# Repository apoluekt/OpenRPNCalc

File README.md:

# OpenRPNCalc
Open-source and open-hardware scientific RPN calculator

## Introduction

OpenRPNCalc is a scientific calculator based on the STM32 microcontroller. Its source code, schematics, and PCB design files are released under an open license. The goal is to develop a hardware platform with the following features: 
  * Reproducible without special tools, using only boards produced by PCB prototyping services
  * A customizable keyboard to accommodate specific needs (such as RPN or algebraic logic, custom functions)
  * Low power consumption and long battery life
  * A high-quality, compact and sturdy enclosure

The hardware is inspired by the [SwissMicros](https://www.swissmicros.com/products) calculators, but is designed from scratch. The calculator features: 

  * [Reverse Polish notation](https://www.hpmuseum.org/rpn.htm) with a large stack (up to 100 elements)
  * Double-precision arithmetic
  * "Standard" scientific calculator functions (trigonometric, logarithms, exponentiation, square root and power)
  * Error function (erf) and its inverse (erfinv), Gamma and log(Gamma) functions, combinations and permutations, p-values for Poisson, Gaussian, and chi-squared distributions
  * Fixed, scientific (SCI) and engineering (ENG) display modes (including SI prefixes in ENG mode), with adjustable precision from 3 to 10 digits
  * Calculations with uncertainties using error propagation (UNCERT mode) - a feature rarely found in software calculators and almost unheard of in hardware calculators
  * Formulas from relativistic kinematics (centre-of-mass two-body decay momentum, conversion between angle and pseudorapidity, beta and gamma factors)
  * Statistical functions: mean (or weighted mean in UNCERT mode), RMS, chi-squared of a series of values (only in UNCERT mode). 
  * 100 memory registers
  * Power consumption: 0.6mA running at 16MHz, 16 uA in standby mode with the LCD on, and 5 uA with the LCD off.
  * Optional HP48 keyboard files, with the aim to run [DB48x](https://48calc.org/) (this is still very much WIP)

## Hardware overview

The calculator is built around a low-power 32-bit ARM microcontroller, the [STM32U385](https://www.st.com/en/microcontrollers-microprocessors/stm32u385rg.html). The display is a Sharp memory LCD module, the [LS027B7DH01](https://www.sharpsde.com/products/displays/model/LS027B7DH01/) (400x240 pixel monochrome). The keyboard uses light-touch tactile switches, specifically the Panasonic [EVPBT1C4A000](https://industry.panasonic.com/global/en/products/control/switch/light-touch/number/evpbt1c4a000) (50g actuation force). All electronics are powered by a 3V lithium battery (CR2032), which should be sufficient for several years of operation. 

The enclosure is designed as a stack of multiple PCBs. The front and back panels are aluminium PCBs with a white solder mask and black silkscreen. The keys are also made of PCB, with labels printed as silkscreen. All components are kept together with six M2 standoffs and twelve flat-head screws. The enclosure dimensions are 139 x 73 x 8 mm. 

## Repository contents

   * [Code](Code): STM32 firmware developed using STM32Cube IDE
   * [Hardware](Hardware): Schematic and PCB design files for KiCad, PCB production files
   * [Doc](Doc): Documentation and images
   * [Emulator](Emulator): Online emulator files to be deployed to github-pages or other web hosting

## Documentation

   * [Schematics and parts](Doc/schematics.md) of the PCBs and the list of electronic components and other parts with links to datasheets
   * [PCB design](Doc/pcb_design.md): images of the PCB layers and their functions
   * [Case and keyboard assembly](Doc/assembly.md): photos of the insides of the calculator, assembly instructions
   * [Firmware](Code/README.md): code structure and flashing instructions

## Emulator 

[Online emulator](https://apoluekt.github.io/OpenRPNCalc/Emulator/), based on the original calculator firmware extended with Emscripten and Raylib

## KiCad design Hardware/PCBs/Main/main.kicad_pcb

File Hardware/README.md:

# Hardware design files

Contents of this folder: 

* [PCBs](PCBs): KiCad design files (schematic and PCBs) for all sevel layers. Where appropriate, Python files are also provided to produce silkscreen labels, place components, and make edge cuts.
* [production](production): Production files created in KiCad (Gerber files, bill of materials, position files for assembly service) for each of the 7 PCBs. These can normally be submitted to the PCB prototyping service without modifications.

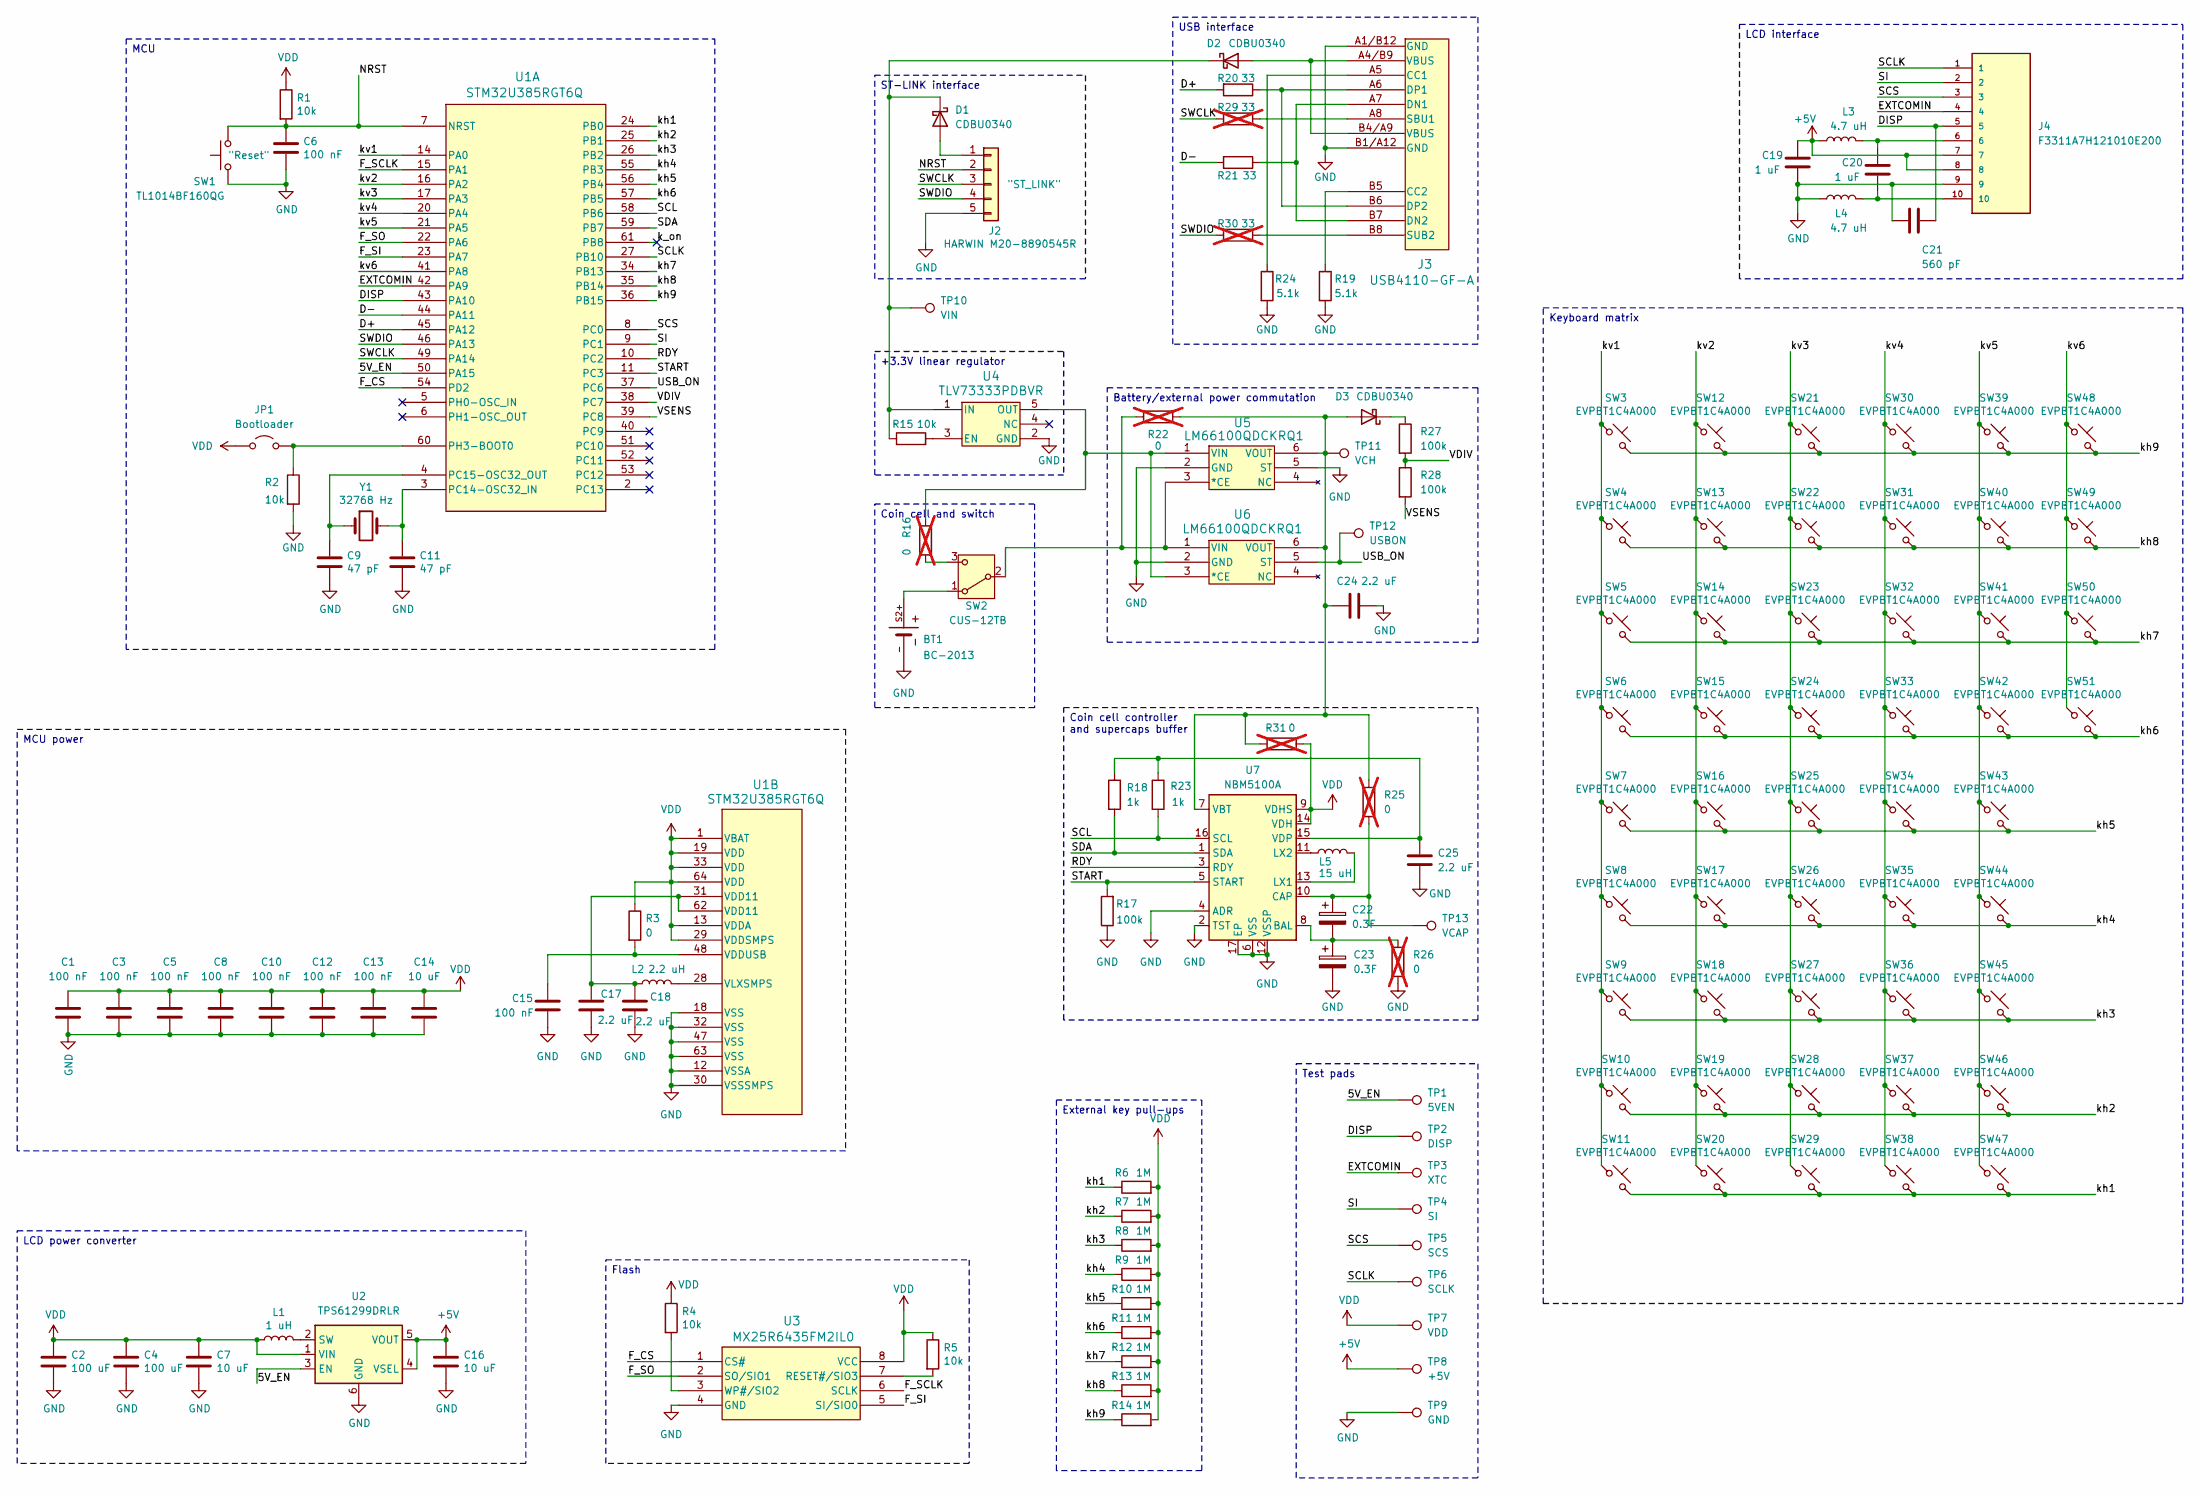
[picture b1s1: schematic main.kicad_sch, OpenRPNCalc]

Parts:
BT1: BC-2013; BAT_BC-2013; PARTREV D
C1, C3, C5, C6, C8, C10, C12, C13, C15: 100 nF; C_0603_1608Metric_Pad1.08x0.95mm_HandSolder
C2, C4: 100 uF; C_0805_2012Metric_Pad1.18x1.45mm_HandSolder
C7, C14, C16: 10 uF; C_0603_1608Metric_Pad1.08x0.95mm_HandSolder
C9, C11: 47 pF; C_0603_1608Metric_Pad1.08x0.95mm_HandSolder
C17, C18, C24, C25: 2.2 uF; C_0603_1608Metric_Pad1.08x0.95mm_HandSolder
C19, C20: 1 uF; C_0603_1608Metric_Pad1.08x0.95mm_HandSolder
C21: 560 pF; C_0603_1608Metric_Pad1.08x0.95mm_HandSolder
C22, C23: 0.3F; Supercap_4x10
D1, D2, D3: CDBU0340; D_0603_1608Metric_Pad1.05x0.95mm_HandSolder
J2: HARWIN M20-8890545R; HARWIN_M20-8890545R
J3: USB4110-GF-A; GCT_USB4110GFA
J4: F3311A7H121010E200; AMPHENOL_F3311A7H121010E200; PARTREV A
JP1: Bootloader; R_0603_1608Metric_Pad0.98x0.95mm_HandSolder
L1: 1 uH; L_0805_2012Metric_Pad1.15x1.40mm_HandSolder
L2: 2.2 uH; L_0805_2012Metric_Pad1.05x1.20mm_HandSolder
L3, L4: 4.7 uH; L_0805_2012Metric_Pad1.15x1.40mm_HandSolder
L5: 15 uH; L_0805_2012Metric_Pad1.05x1.20mm_HandSolder
R1, R2, R4, R5, R15: 10k; R_0603_1608Metric_Pad0.98x0.95mm_HandSolder
R3: 0; R_0603_1608Metric_Pad0.98x0.95mm_HandSolder
R6, R7, R8, R9, R10, R11, R12, R13, R14: 1M; R_0603_1608Metric_Pad0.98x0.95mm_HandSolder
R16, R22, R25, R26, R31: 0; R_0603_1608Metric_Pad0.98x0.95mm_HandSolder; not fitted
R17, R27, R28: 100k; R_0603_1608Metric_Pad0.98x0.95mm_HandSolder
R18, R23: 1k; R_0603_1608Metric_Pad0.98x0.95mm_HandSolder
R19, R24: 5.1k; R_0603_1608Metric_Pad0.98x0.95mm_HandSolder
R20, R21: 33; R_0603_1608Metric_Pad0.98x0.95mm_HandSolder
R29, R30: 33; R_0603_1608Metric_Pad0.98x0.95mm_HandSolder; not fitted
SW1: TL1014BF160QG; TL1014BF160QG_EWI
SW2: CUS-12TB; CUS-12TB_NDC
SW3, SW4, SW5, SW6, SW7, SW8, SW9, SW10, SW11, SW12, SW13, SW14, SW15, SW16, SW17, SW18, SW19, SW20, SW21, SW22, SW23, SW24, SW25, SW26, SW27, SW28, SW29, SW30, SW31, SW32, SW33, SW34, SW35, SW36, SW37, SW38, SW39, SW40, SW41, SW42, SW43, SW44, SW45, SW46, SW47, SW48, SW49, SW50, SW51: EVPBT1C4A000; SW_SPST_EVQQ2
TP1: 5VEN; TestPoint_Pad_D2.0mm
TP2: DISP; TestPoint_Pad_D2.0mm
TP3: XTC; TestPoint_Pad_D2.0mm
TP4: SI; TestPoint_Pad_D2.0mm
TP5: SCS; TestPoint_Pad_D2.0mm
TP6: SCLK; TestPoint_Pad_D2.0mm
TP7: VDD; TestPoint_Pad_D2.0mm
TP8: +5V; TestPoint_Pad_D2.0mm
TP9: GND; TestPoint_Pad_D2.0mm
TP10: VIN; TestPoint_Pad_D2.0mm
TP11: VCH; TestPoint_Pad_D2.0mm
TP12: USBON; TestPoint_Pad_D2.0mm
TP13: VCAP; TestPoint_Pad_D2.0mm
U1: STM32U385RGT6Q; LQFP64_STM
U2: TPS61299DRLR; SOT-563
U3: MX25R6435FM2IL0; SOP_8L_200_MAC
U4: TLV73333PDBVR; DBV0005A_N
U5, U6: LM66100QDCKRQ1; SC70-6_DCK_TEX
U7: NBM5100A; DHVQFN-16-1EP_2.5x3.5mm_P0.5mm_EP1x2mm
Y1: 32768 Hz; Crystal_SMD_2012-2Pin_2.0x1.2mm_HandSoldering

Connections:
+5V: C16.1, C19.1, J4.7, J4.8, L3.1, TP8.1, U2.4 (VSEL), U2.5 (VOUT)
/5V_EN: TP1.1, U1.50 (PA15), U2.3 (EN)
/D+: R20.2, U1.45 (PA12)
/D-: R21.2, U1.44 (PA11)
/DISP: C21.1, J4.5, TP2.1, U1.43 (PA10)
/EXTCOMIN: J4.4, TP3.1, U1.42 (PA9)
/F_CS: U1.54 (PD2), U3.1 (CS#)
/F_SCLK: U1.15 (PA1), U3.6 (SCLK)
/F_SI: U1.23 (PA7), U3.5 (SI/SIO0)
/F_SO: U1.22 (PA6), U3.2 (SO/SIO1)
/NRST: C6.1, J2.2, R1.2, SW1.1, U1.7 (NRST)
/RDY: U1.10 (PC2), U7.3 (RDY)
/SCL: R23.2, U1.58 (PB6), U7.16 (SCL)
/SCLK: J4.1, TP6.1, U1.27 (PB10)
/SCS: J4.3, TP5.1, U1.8 (PC0)
/SDA: R18.2, U1.59 (PB7), U7.1 (SDA)
/SI: J4.2, TP4.1, U1.9 (PC1)
/START: R17.2, U1.11 (PC3), U7.5 (START)
/SWCLK: J2.3, R29.2, U1.49 (PA14)
/SWDIO: J2.4, R30.2, U1.46 (PA13)
/USB_ON: TP12.1, U1.37 (PC6), U6.5 (ST)
/VDIV: R27.2, R28.1, U1.38 (PC7)
/VSENS: R28.2, U1.39 (PC8)
/k_on: U1.61 (PB8)
/kh1: R6.1, SW11.2, SW20.2, SW29.2, SW38.2, SW47.2, U1.24 (PB0)
/kh2: R7.1, SW10.2, SW19.2, SW28.2, SW37.2, SW46.2, U1.25 (PB1)
/kh3: R8.1, SW9.2, SW18.2, SW27.2, SW36.2, SW45.2, U1.26 (PB2)
/kh4: R9.1, SW8.2, SW17.2, SW26.2, SW35.2, SW44.2, U1.55 (PB3)
/kh5: R10.1, SW7.2, SW16.2, SW25.2, SW34.2, SW43.2, U1.56 (PB4)
/kh6: R11.1, SW6.2, SW15.2, SW24.2, SW33.2, SW42.2, SW51.2, U1.57 (PB5)
/kh7: R12.1, SW5.2, SW14.2, SW23.2, SW32.2, SW41.2, SW50.2, U1.34 (PB13)
/kh8: R13.1, SW4.2, SW13.2, SW22.2, SW31.2, SW40.2, SW49.2, U1.35 (PB14)
/kh9: R14.1, SW3.2, SW12.2, SW21.2, SW30.2, SW39.2, SW48.2, U1.36 (PB15)
/kv1: SW3.1, SW4.1, SW5.1, SW6.1, SW7.1, SW8.1, SW9.1, SW10.1, SW11.1, U1.14 (PA0)
/kv2: SW12.1, SW13.1, SW14.1, SW15.1, SW16.1, SW17.1, SW18.1, SW19.1, SW20.1, U1.16 (PA2)
/kv3: SW21.1, SW22.1, SW23.1, SW24.1, SW25.1, SW26.1, SW27.1, SW28.1, SW29.1, U1.17 (PA3)
/kv4: SW30.1, SW31.1, SW32.1, SW33.1, SW34.1, SW35.1, SW36.1, SW37.1, SW38.1, U1.20 (PA4)
/kv5: SW39.1, SW40.1, SW41.1, SW42.1, SW43.1, SW44.1, SW45.1, SW46.1, SW47.1, U1.21 (PA5)
/kv6: SW48.1, SW49.1, SW50.1, SW51.1, U1.41 (PA8)
GND: BT1.-, C1.1, C2.2, C3.1, C4.2, C5.1, C6.2, C7.2, C8.1, C9.2, C10.1, C11.2, C12.1, C13.1, C14.1, C15.2, C16.2, C17.2, C18.2, C19.2, C21.2, C23.2, C24.2, C25.2, J2.5, J3.A1/B12 (GND), J3.B1/A12 (GND), J4.9, L4.1, R2.2, R17.1, R19.2, R24.2, R26.2, SW1.2, TP9.1, U1.12 (VSSA), U1.18 (VSS), U1.30 (VSSSMPS), U1.32 (VSS), U1.47 (VSS), U1.63 (VSS), U2.6 (GND), U3.4 (GND), U4.2 (GND), U5.2 (GND), U5.5 (ST), U6.2 (GND), U7.2 (TST), U7.4 (ADR), U7.6 (VSS), U7.12 (VSSP), U7.17 (EP)
unnamed: C17.1, C18.1, L2.1, U1.31 (VDD11), U1.62 (VDD11)
unnamed: C20.1, J4.6, L3.2
unnamed: C20.2, J4.10, L4.2
unnamed: D1.2 (A), J2.1
unnamed: D1.1 (K), D2.1 (K), R15.1, TP10.1, U4.1 (IN)
unnamed: D2.2 (A), J3.A4/B9 (VBUS), J3.B4/A9 (VBUS)
unnamed: C24.1, D3.2 (A), R22.1, R25.1, R31.1, TP11.1, U5.6 (VOUT), U6.6 (VOUT), U7.7 (VBT)
unnamed: D3.1 (K), R27.1
unnamed: J3.A5 (CC1), R24.1
unnamed: J3.B5 (CC2), R19.1
unnamed: J3.A7 (DN1), J3.B7 (DN2), R21.1
unnamed: J3.A6 (DP1), J3.B6 (DP2), R20.1
unnamed: J3.A8 (SBU1), R29.1
unnamed: J3.B8 (SUB2), R30.1
unnamed: JP1.2 (B), R2.1, U1.60 (PH3-BOOT0)
unnamed: BT1.S2+, SW2.1 (A)
unnamed: R22.2, SW2.2 (B), U5.3 (*CE), U6.1 (VIN)
unnamed: R16.1, SW2.3 (C)
unnamed: C11.1, U1.3 (PC14-OSC32_IN), Y1.2
unnamed: C9.1, U1.4 (PC15-OSC32_OUT), Y1.1
unnamed: C15.1, R3.2, U1.48 (VDDUSB)
unnamed: L2.2, U1.28 (VLXSMPS)
unnamed: L1.2, U2.2 (SW)
unnamed: R5.2, U3.7 (RESET#/SIO3)
unnamed: R4.2, U3.3 (WP#/SIO2)
unnamed: R15.2, U4.3 (EN)
unnamed: R16.2, U4.5 (OUT), U5.1 (VIN), U6.3 (*CE)
unnamed: C22.2, C23.1, R26.1, U7.8 (BAL)
unnamed: C22.1, R25.2, TP13.1, U7.10 (CAP)
unnamed: L5.2, U7.13 (LX1)
unnamed: L5.1, U7.11 (LX2)
unnamed: C25.1, R18.1, R23.1, U7.15 (VDP)
VDD: C1.2, C2.1, C3.2, C4.1, C5.2, C7.1, C8.2, C10.2, C12.2, C13.2, C14.2, JP1.1 (A), L1.1, R1.1, R3.1, R4.1, R5.1, R6.2, R7.2, R8.2, R9.2, R10.2, R11.2, R12.2, R13.2, R14.2, R31.2, TP7.1, U1.1 (VBAT), U1.13 (VDDA), U1.19 (VDD), U1.29 (VDDSMPS), U1.33 (VDD), U1.64 (VDD), U2.1 (VIN), U3.8 (VCC), U7.9 (VDHS), U7.14 (VDH)

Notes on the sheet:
MCU
Keyboard matrix
+3.3V linear regulator
Flash
LCD interface
MCU power
Battery/external power commutation
Coin cell controller and supercaps buffer
Coin cell and switch
ST-LINK interface
Test pads
LCD power converter
USB interface
External key pull-ups

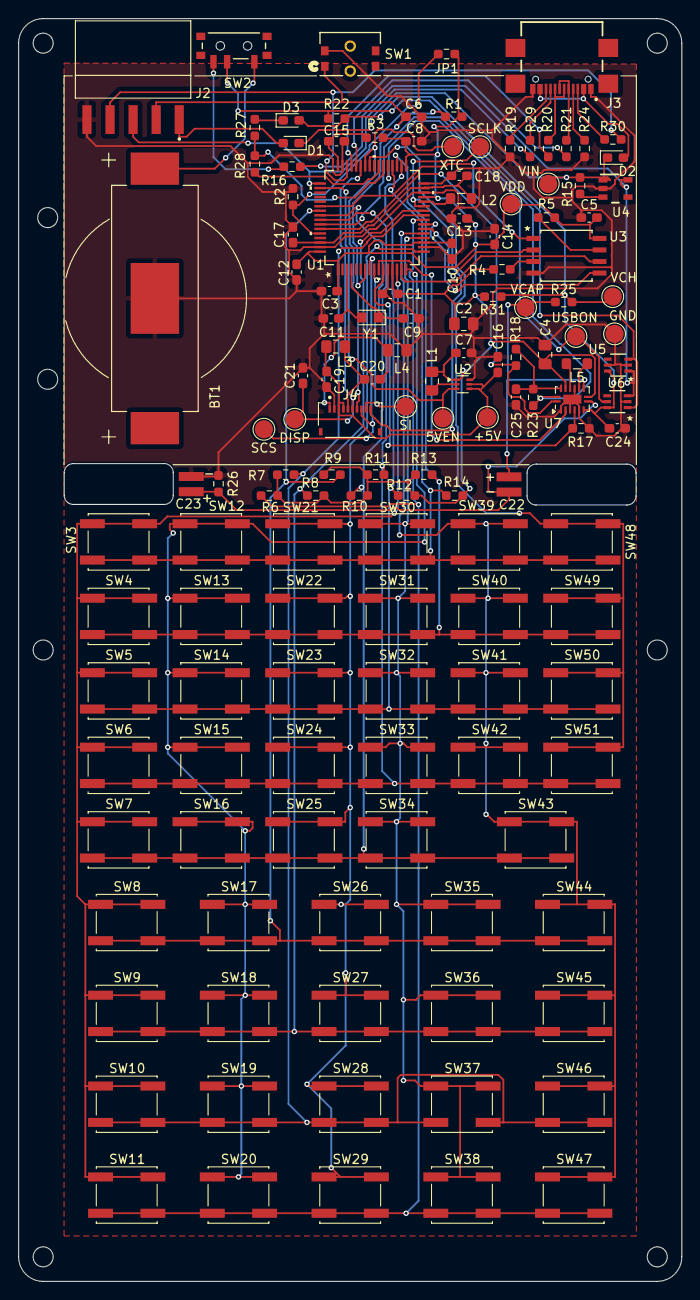
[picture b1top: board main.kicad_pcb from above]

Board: 2 copper layers, 73.0 x 139.0 mm, 141 parts (0 on the bottom side), 72 nets.

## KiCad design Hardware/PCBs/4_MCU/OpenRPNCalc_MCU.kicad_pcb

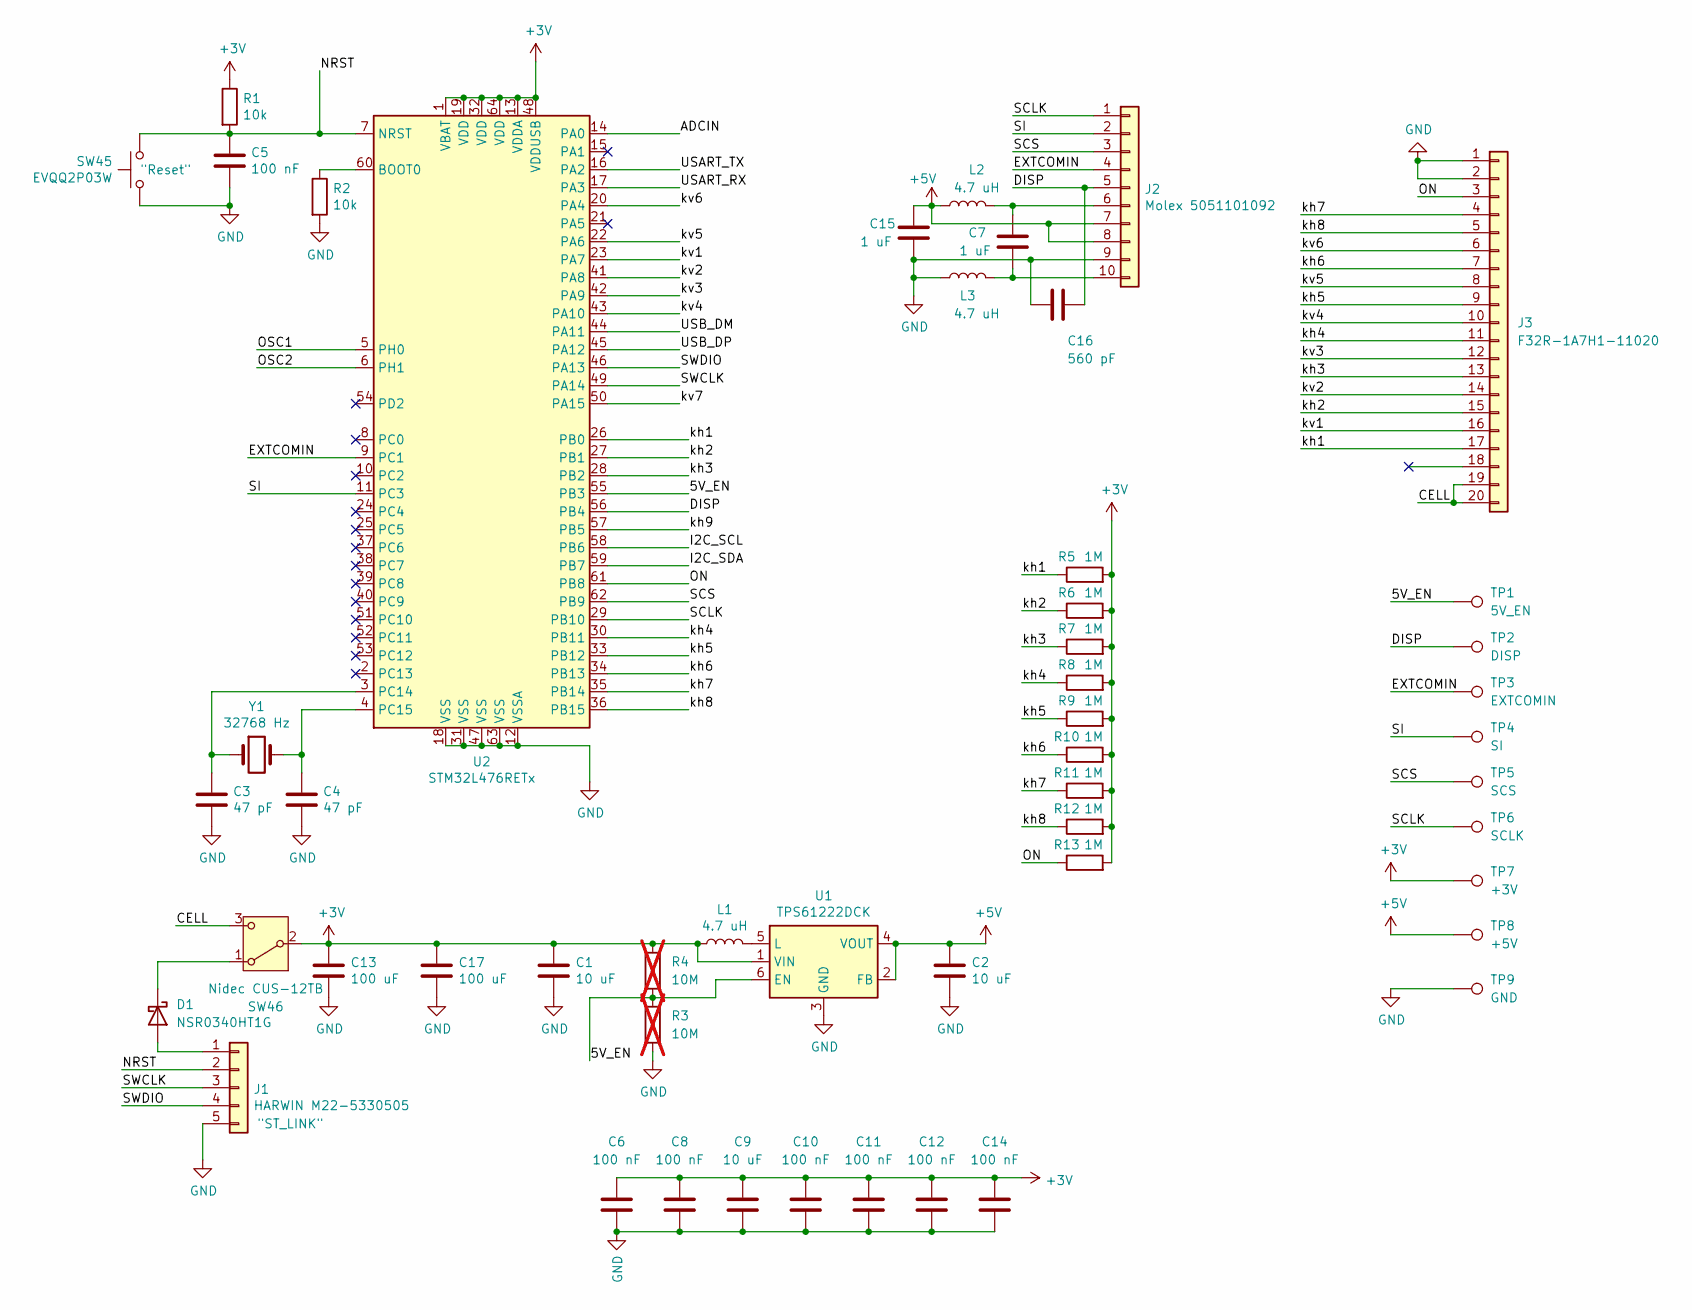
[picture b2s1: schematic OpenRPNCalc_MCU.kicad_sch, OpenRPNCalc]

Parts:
C1, C2, C9: 10 uF; C_0603_1608Metric_Pad1.08x0.95mm_HandSolder
C3, C4: 47 pF; C_0603_1608Metric_Pad1.08x0.95mm_HandSolder
C5, C6, C8, C10, C11, C12, C14: 100 nF; C_0603_1608Metric_Pad1.08x0.95mm_HandSolder
C7, C15: 1 uF; C_0603_1608Metric_Pad1.08x0.95mm_HandSolder
C13, C17: 100 uF; C_1206_3216Metric_Pad1.33x1.80mm_HandSolder
C16: 560 pF; C_0603_1608Metric_Pad1.08x0.95mm_HandSolder
D1: NSR0340HT1G; D_SOD-323_HandSoldering
J1: HARWIN M22-5330505; HARWIN_M22-5330505
J2: Molex 5051101092; CON_5051101092_MOL
J3: F32R-1A7H1-11020; AMPHENOL_F32R-1A7H1-11020
L1, L2, L3: 4.7 uH; L_0805_2012Metric_Pad1.15x1.40mm_HandSolder
R1, R2: 10k; R_0603_1608Metric_Pad0.98x0.95mm_HandSolder
R3, R4: 10M; R_0603_1608Metric_Pad0.98x0.95mm_HandSolder; not fitted
R5, R6, R7, R8, R9, R10, R11, R12, R13: 1M; R_0603_1608Metric_Pad0.98x0.95mm_HandSolder
SW45: EVQQ2P03W; SW_SPST_EVQQ2
SW46: Nidec CUS-12TB; CUS-12TB_NDC
TP1: 5V_EN; TestPoint_Pad_D2.0mm
TP2: DISP; TestPoint_Pad_D2.0mm
TP3: EXTCOMIN; TestPoint_Pad_D2.0mm
TP4: SI; TestPoint_Pad_D2.0mm
TP5: SCS; TestPoint_Pad_D2.0mm
TP6: SCLK; TestPoint_Pad_D2.0mm
TP7: +3V; TestPoint_Pad_D2.0mm
TP8: +5V; TestPoint_Pad_D2.0mm
TP9: GND; TestPoint_Pad_D2.0mm
U1: TPS61222DCK; Texas_R-PDSO-G6
U2: STM32L476RETx; LQFP-64_10x10mm_P0.5mm
Y1: 32768 Hz; Crystal_SMD_2012-2Pin_2.0x1.2mm_HandSoldering

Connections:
+5V: C2.1, C15.1, J2.7, J2.8, L2.1, TP8.1, U1.2 (FB), U1.4 (VOUT)
+BATT: C1.1, C6.2, C8.2, C9.2, C10.2, C11.2, C12.2, C13.1, C14.2, C17.1, L1.1, R1.1, R4.1, R5.2, R6.2, R7.2, R8.2, R9.2, R10.2, R11.2, R12.2, R13.2, SW46.2 (B), TP7.1, U1.1 (VIN), U2.1 (VBAT), U2.13 (VDDA), U2.19 (VDD), U2.32 (VDD), U2.48 (VDDUSB), U2.64 (VDD)
/5V_EN: R3.1, R4.2, TP1.1, U1.6 (EN), U2.55 (PB3)
/ADCIN: U2.14 (PA0)
/CELL: J3.19, J3.20, SW46.3 (C)
/DISP: C16.1, J2.5, TP2.1, U2.56 (PB4)
/EXTCOMIN: J2.4, TP3.1, U2.9 (PC1)
/I2C_SCL: U2.58 (PB6)
/I2C_SDA: U2.59 (PB7)
/NRST: C5.1, J1.2, R1.2, SW45.1, U2.7 (NRST)
/ON: J3.3, R13.1, U2.61 (PB8)
/OSC1: U2.5 (PH0)
/OSC2: U2.6 (PH1)
/SCLK: J2.1, TP6.1, U2.29 (PB10)
/SCS: J2.3, TP5.1, U2.62 (PB9)
/SI: J2.2, TP4.1, U2.11 (PC3)
/SWCLK: J1.3, U2.49 (PA14)
/SWDIO: J1.4, U2.46 (PA13)
/USART_RX: U2.17 (PA3)
/USART_TX: U2.16 (PA2)
/USB_DM: U2.44 (PA11)
/USB_DP: U2.45 (PA12)
/kh1: J3.17, R5.1, U2.26 (PB0)
/kh2: J3.15, R6.1, U2.27 (PB1)
/kh3: J3.13, R7.1, U2.28 (PB2)
/kh4: J3.11, R8.1, U2.30 (PB11)
/kh5: J3.9, R9.1, U2.33 (PB12)
/kh6: J3.7, R10.1, U2.34 (PB13)
/kh7: J3.4, R11.1, U2.35 (PB14)
/kh8: J3.5, R12.1, U2.36 (PB15)
/kh9: U2.57 (PB5)
/kv1: J3.16, U2.23 (PA7)
/kv2: J3.14, U2.41 (PA8)
/kv3: J3.12, U2.42 (PA9)
/kv4: J3.10, U2.43 (PA10)
/kv5: J3.8, U2.22 (PA6)
/kv6: J3.6, U2.20 (PA4)
/kv7: U2.50 (PA15)
GND: C1.2, C2.2, C3.2, C4.2, C5.2, C6.1, C8.1, C9.1, C10.1, C11.1, C12.1, C13.2, C14.1, C15.2, C16.2, C17.2, J1.5, J2.9, J3.1, J3.2, L3.1, R2.2, R3.2, SW45.2, TP9.1, U1.3 (GND), U2.12 (VSSA), U2.18 (VSS), U2.31 (VSS), U2.47 (VSS), U2.63 (VSS)
unnamed: D1.2 (A), J1.1
unnamed: D1.1 (K), SW46.1 (A)
unnamed: C7.1, J2.6, L2.2
unnamed: C7.2, J2.10, L3.2
unnamed: L1.2, U1.5 (L)
unnamed: R2.1, U2.60 (BOOT0)
unnamed: C3.1, U2.3 (PC14), Y1.1
unnamed: C4.1, U2.4 (PC15), Y1.2

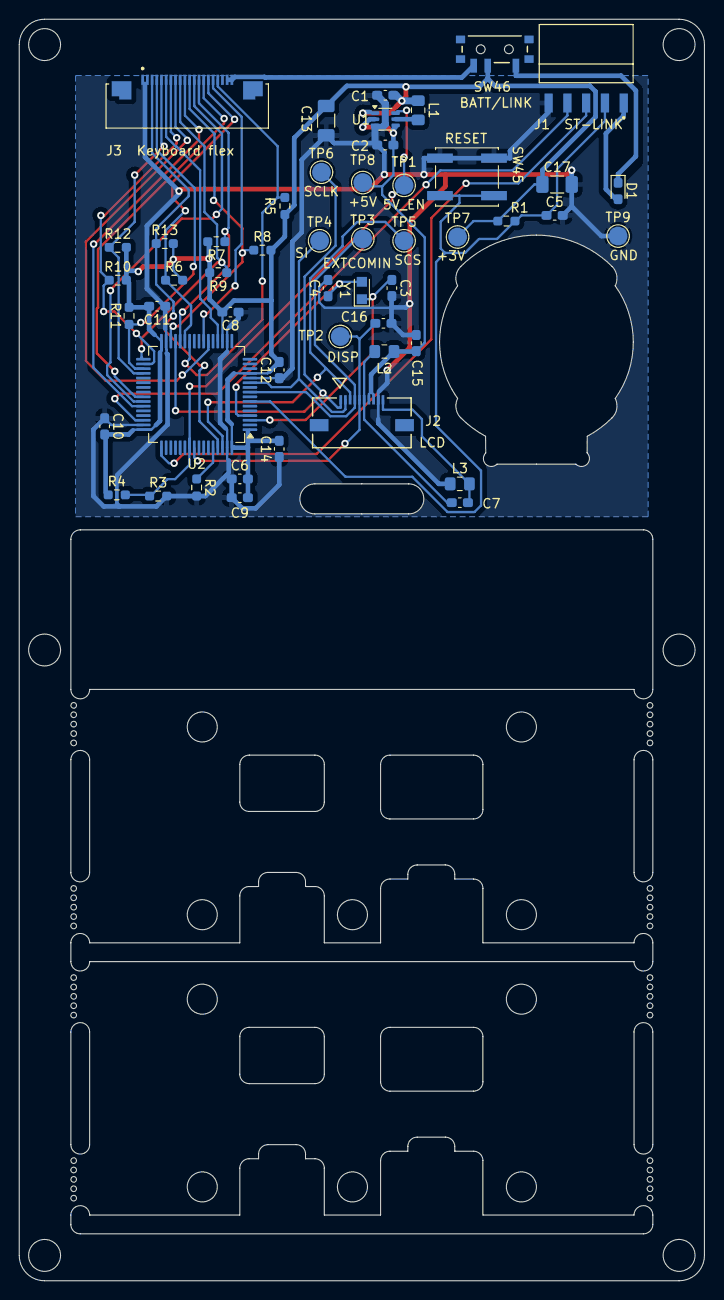
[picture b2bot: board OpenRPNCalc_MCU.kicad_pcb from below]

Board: 2 copper layers, 73.0 x 134.4 mm, 51 parts (51 on the bottom side), 36 nets.

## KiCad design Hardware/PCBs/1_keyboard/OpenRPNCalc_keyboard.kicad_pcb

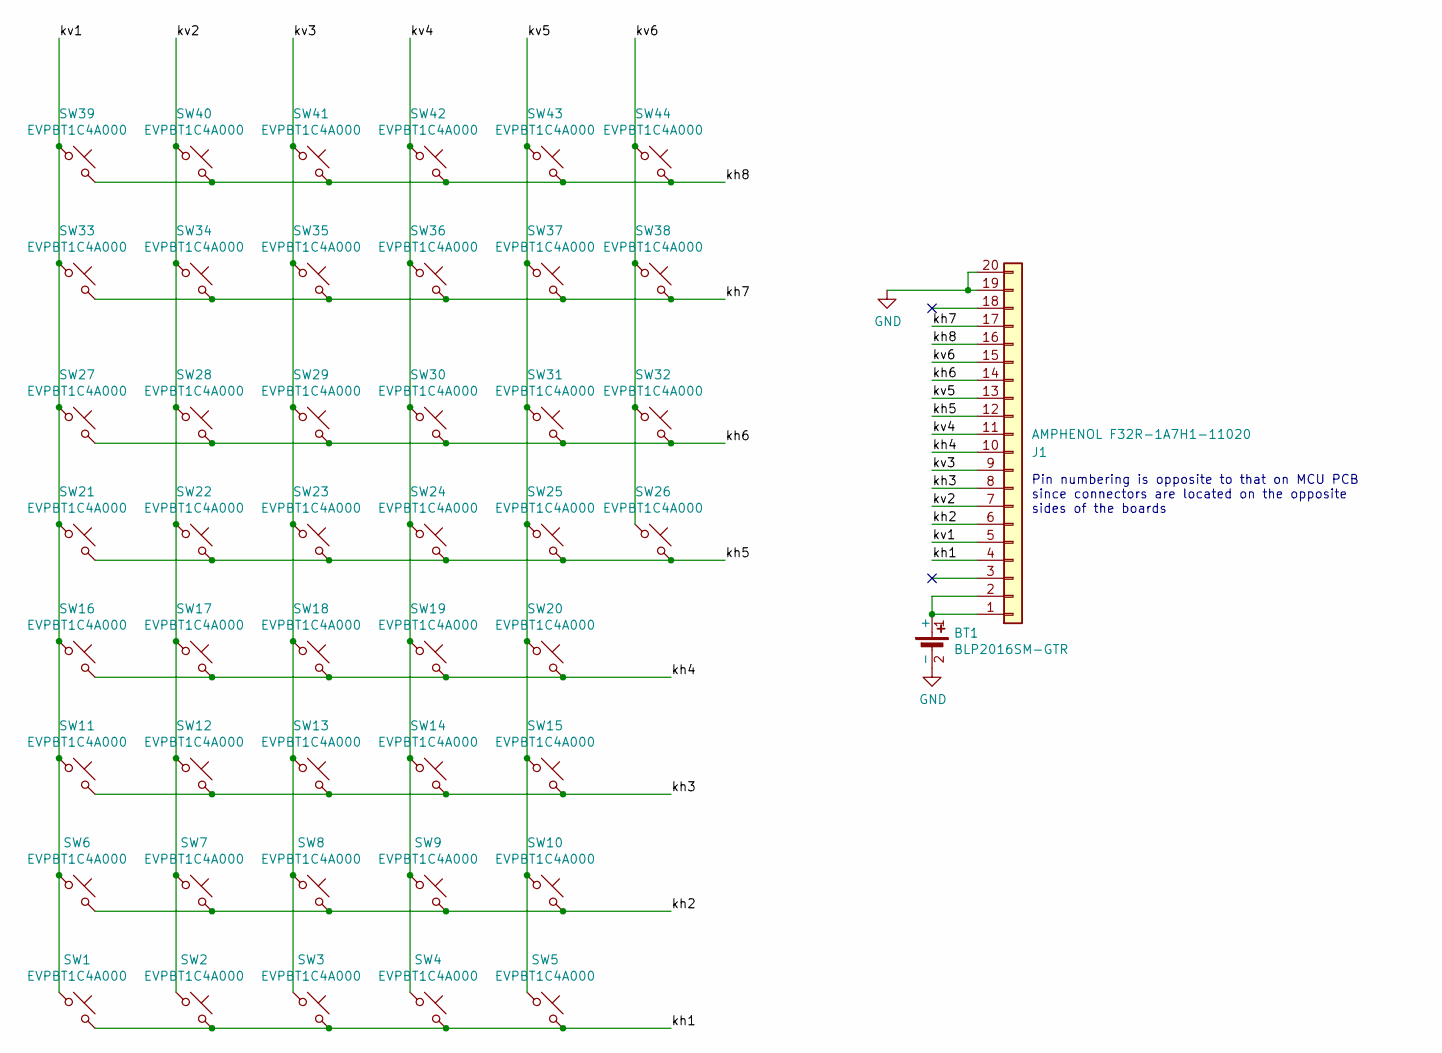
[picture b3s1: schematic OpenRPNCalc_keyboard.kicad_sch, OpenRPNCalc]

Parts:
BT1: BLP2016SM-GTR; BAT_BLP2016SM-G
J1: AMPHENOL F32R-1A7H1-11020; AMPHENOL_F32R-1A7H1-11020
SW1, SW2, SW3, SW4, SW5, SW6, SW7, SW8, SW9, SW10, SW11, SW12, SW13, SW14, SW15, SW16, SW17, SW18, SW19, SW20, SW21, SW22, SW23, SW24, SW25, SW26, SW27, SW28, SW29, SW30, SW31, SW32, SW33, SW34, SW35, SW36, SW37, SW38, SW39, SW40, SW41, SW42, SW43, SW44: EVPBT1C4A000; SW_SPST_EVQQ2

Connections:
/kh1: J1.4, SW1.2, SW2.2, SW3.2, SW4.2, SW5.2
/kh2: J1.6, SW6.2, SW7.2, SW8.2, SW9.2, SW10.2
/kh3: J1.8, SW11.2, SW12.2, SW13.2, SW14.2, SW15.2
/kh4: J1.10, SW16.2, SW17.2, SW18.2, SW19.2, SW20.2
/kh5: J1.12, SW21.2, SW22.2, SW23.2, SW24.2, SW25.2, SW26.2
/kh6: J1.14, SW27.2, SW28.2, SW29.2, SW30.2, SW31.2, SW32.2
/kh7: J1.17, SW33.2, SW34.2, SW35.2, SW36.2, SW37.2, SW38.2
/kh8: J1.16, SW39.2, SW40.2, SW41.2, SW42.2, SW43.2, SW44.2
/kv1: J1.5, SW1.1, SW6.1, SW11.1, SW16.1, SW21.1, SW27.1, SW33.1, SW39.1
/kv2: J1.7, SW2.1, SW7.1, SW12.1, SW17.1, SW22.1, SW28.1, SW34.1, SW40.1
/kv3: J1.9, SW3.1, SW8.1, SW13.1, SW18.1, SW23.1, SW29.1, SW35.1, SW41.1
/kv4: J1.11, SW4.1, SW9.1, SW14.1, SW19.1, SW24.1, SW30.1, SW36.1, SW42.1
/kv5: J1.13, SW5.1, SW10.1, SW15.1, SW20.1, SW25.1, SW31.1, SW37.1, SW43.1
/kv6: J1.15, SW26.1, SW32.1, SW38.1, SW44.1
GND: BT1.2 (-), J1.19, J1.20
unnamed: BT1.1 (+), J1.1, J1.2

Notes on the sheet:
Pin numbering is opposite to that on MCU PCB since connectors are located on the opposite sides of the boards

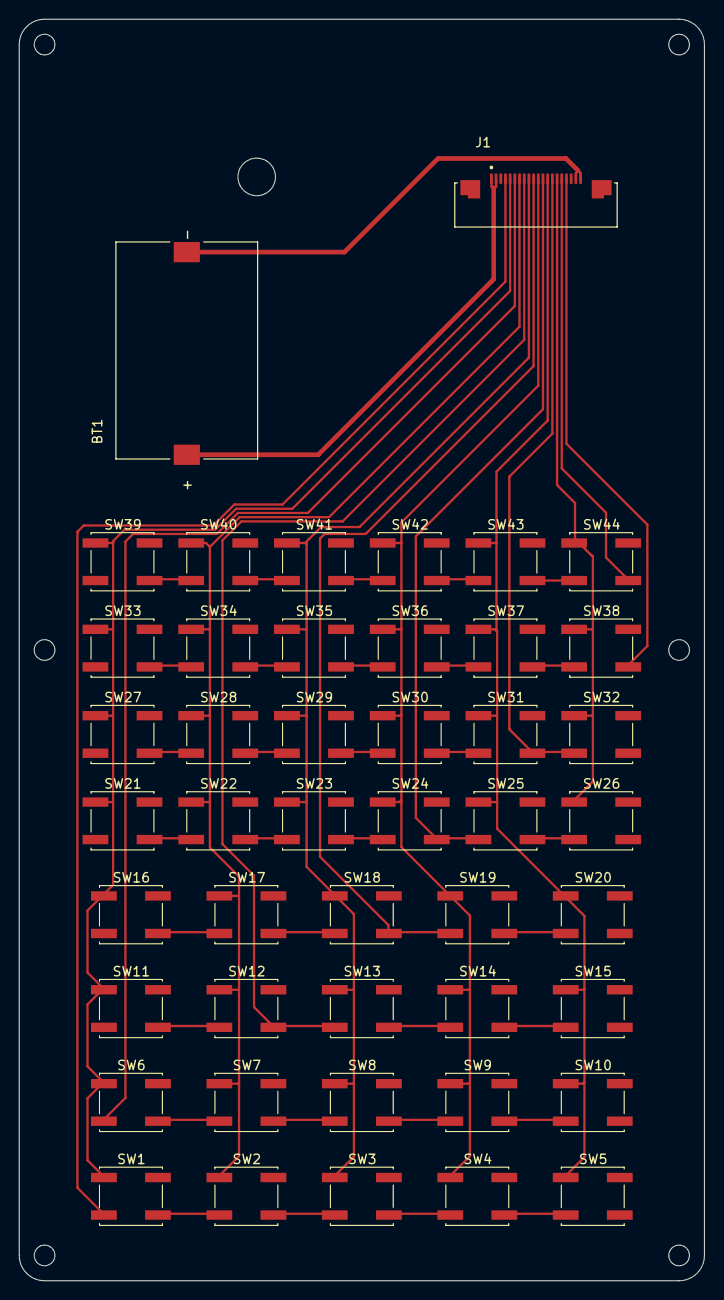
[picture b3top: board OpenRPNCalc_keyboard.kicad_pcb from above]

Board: 2 copper layers, 73.0 x 134.4 mm, 46 parts (0 on the bottom side), 16 nets.

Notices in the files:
Code/Core/Src/main.c:
Copyright (c) 2025 STMicroelectronics.
All rights reserved.
This software is licensed under terms that can be found in the LICENSE file
Code/Src/main.c:
© Copyright (c) 2021 STMicroelectronics.
This software component is licensed by ST under BSD 3-Clause license,
the "License"; You may not use this file except in compliance with the
License. You may obtain a copy of the License at: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
